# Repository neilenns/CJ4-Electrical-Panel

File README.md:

# CJ4 electrical panel for use with MobiFlight

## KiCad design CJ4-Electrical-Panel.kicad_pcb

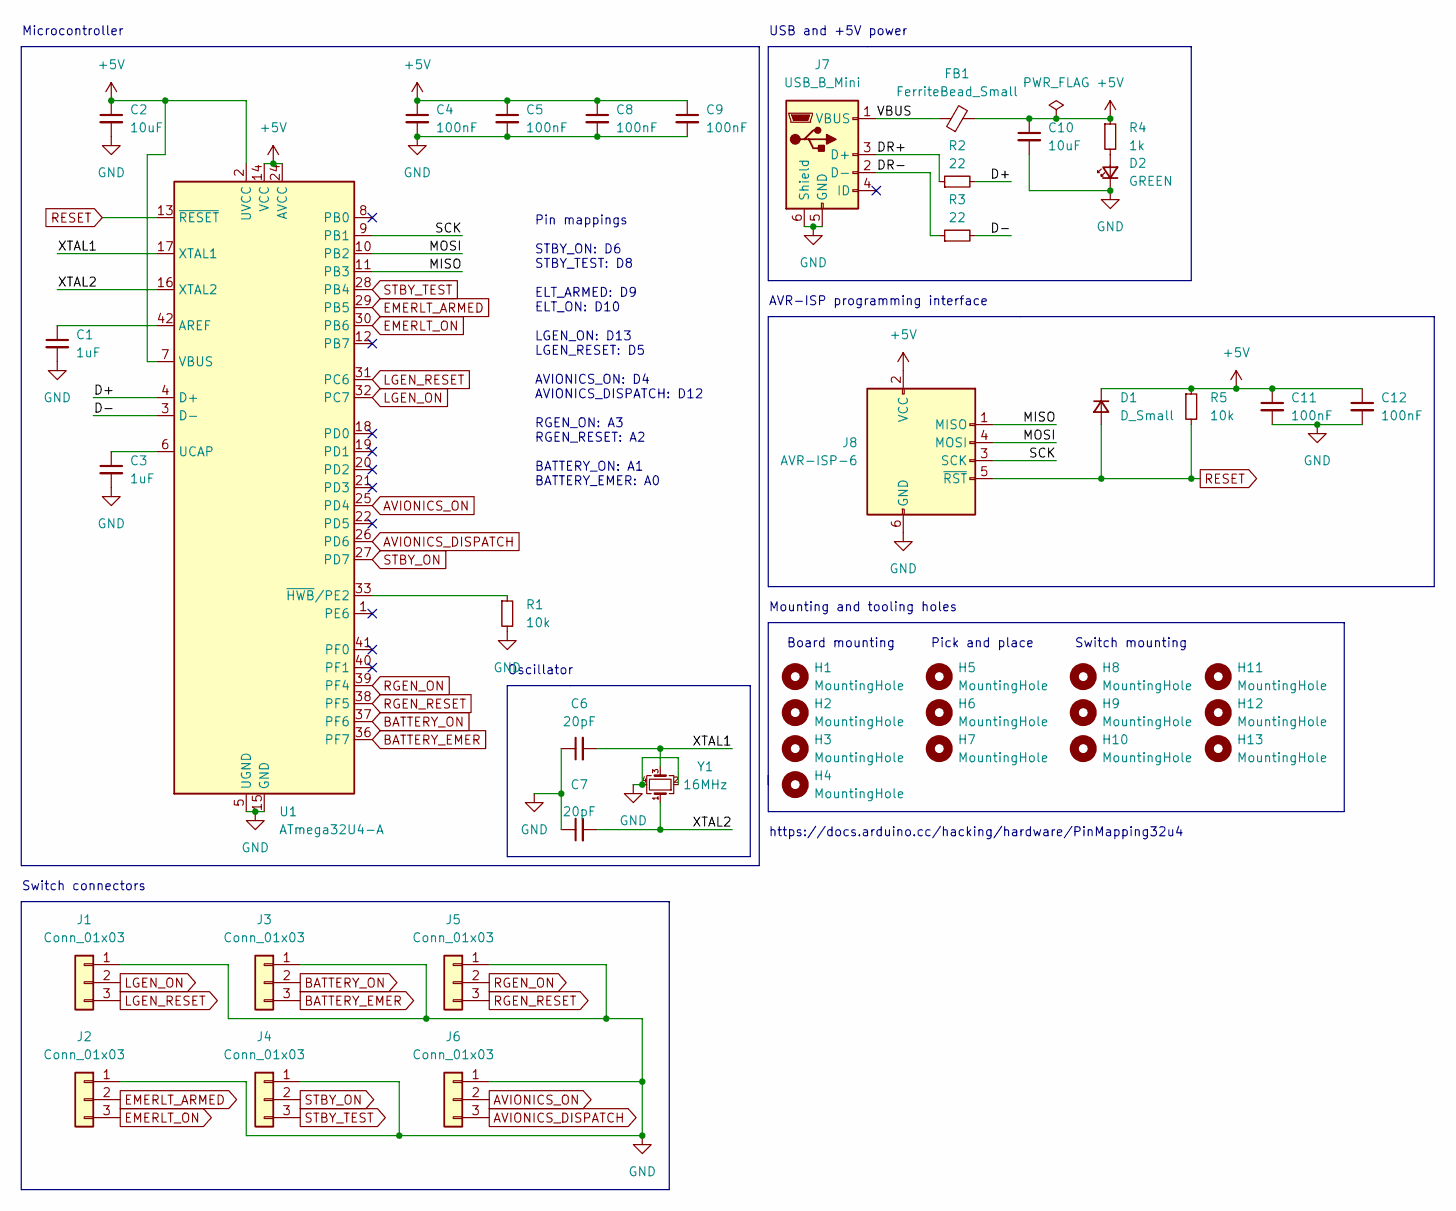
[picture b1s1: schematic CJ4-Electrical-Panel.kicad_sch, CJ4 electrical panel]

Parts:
C1, C3: 1uF; Perfect_0402; JLC 0402
C2, C10: 10uF; Perfect_0402; JLC 0402
C4, C5, C8, C9, C11, C12: 100nF; Perfect_0402; JLC 0402
C6, C7: 20pF; Perfect_0402; JLC 0402
D1: D_Small; D_SOD-323F; JLC SOD-323F
D2: GREEN; LED_0805_2012Metric_Pad1.15x1.40mm_HandSolder; JLC DNP
FB1: FerriteBead_Small; C_0805_2012Metric; JLC 0805
H1, H2, H3, H4: MountingHole; MountingHole_3.2mm_M3; JLC DNP
H5, H6, H7: MountingHole; JLCPCB_Tooling_Hole; JLC DNP
H8, H9, H10, H11, H12, H13: MountingHole; MiniToggleSPDT_screw_mount; JLC DNP
J1, J2, J3, J4, J5, J6: Conn_01x03; JST_XH_B3B-XH-A_1x03_P2.50mm_Vertical; JLC DNP
J7: USB_B_Mini; USB_B_Mini_Amphenol_UE25BE5510H
J8: AVR-ISP-6; Tag-Connect_TC2030-IDC-NL_2x03_P1.27mm_Vertical; JLC DNP
R1, R5: 10k; Perfect_0402; JLC 0402
R2, R3: 22; Perfect_0402; JLC 0402
R4: 1k; Perfect_0402; JLC 0402
U1: ATmega32U4-A; TQFP-44_10x10mm_P0.8mm; JLC DNP
Y1: 16MHz; Crystal_SMD_3225-4Pin_3.2x2.5mm; JLC SMD-CRY-3225_4P

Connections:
+5V: C2.1, C4.1, C5.1, C8.1, C9.1, C10.1, C11.1, C12.1, D1.1 (K), FB1.2, J8.2 (VCC), R4.1, R5.1, U1.2 (UVCC), U1.7 (VBUS), U1.14 (VCC), U1.24 (AVCC), U1.34 (VCC), U1.44 (AVCC)
/D+: R2.2, U1.4 (D+)
/D-: R3.2, U1.3 (D-)
/DR+: J7.3 (D+), R2.1
/DR-: J7.2 (D-), R3.1
/MISO: J8.1 (MISO), U1.11 (PB3)
/MOSI: J8.4 (MOSI), U1.10 (PB2)
/SCK: J8.3 (SCK), U1.9 (PB1)
/VBUS: FB1.1, J7.1 (VBUS)
/XTAL1: C6.2, U1.17 (XTAL1), Y1.3
/XTAL2: C7.2, U1.16 (XTAL2), Y1.1
AVIONICS_DISPATCH: J6.3, U1.26 (PD6)
AVIONICS_ON: J6.2, U1.25 (PD4)
BATTERY_EMER: J3.3, U1.36 (PF7)
BATTERY_ON: J3.2, U1.37 (PF6)
EMERLT_ARMED: J2.2, U1.29 (PB5)
EMERLT_ON: J2.3, U1.30 (PB6)
GND: C1.2, C2.2, C3.2, C4.2, C5.2, C6.1, C7.1, C8.2, C9.2, C10.2, C11.2, C12.2, D2.1 (K), J1.1, J2.1, J3.1, J4.1, J5.1, J6.1, J7.5 (GND), J7.6 (Shield), J8.6 (GND), R1.2, U1.5 (UGND), U1.15 (GND), U1.23 (GND), U1.35 (GND), U1.43 (GND), Y1.2, Y1.4
LGEN_ON: J1.2, U1.32 (PC7)
LGEN_RESET: J1.3, U1.31 (PC6)
unnamed: C1.1, U1.42 (AREF)
unnamed: C3.1, U1.6 (UCAP)
unnamed: D2.2 (A), R4.2
unnamed: R1.1, U1.33 (~HWB/PE2)
RESET: D1.2 (A), J8.5 (~RST), R5.2, U1.13 (~RESET)
RGEN_ON: J5.2, U1.39 (PF4)
RGEN_RESET: J5.3, U1.38 (PF5)
STBY_ON: J4.2, U1.27 (PD7)
STBY_TEST: J4.3, U1.28 (PB4)

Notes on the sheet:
Pick and place
Pin mappings STBY_ON: D6 STBY_TEST: D8 ELT_ARMED: D9 ELT_ON: D10 LGEN_ON: D13 LGEN_RESET: D5 AVIONICS_ON: D4 AVIONICS_DISPATCH: D12 RGEN_ON: A3 RGEN_RESET: A2 BATTERY_ON: A1 BATTERY_EMER: A0
AVR-ISP programming interface
Switch mounting
Board mounting
Microcontroller
Oscillator
Switch connectors
https://docs.arduino.cc/hacking/hardware/PinMapping32u4
Mounting and tooling holes
USB and +5V power

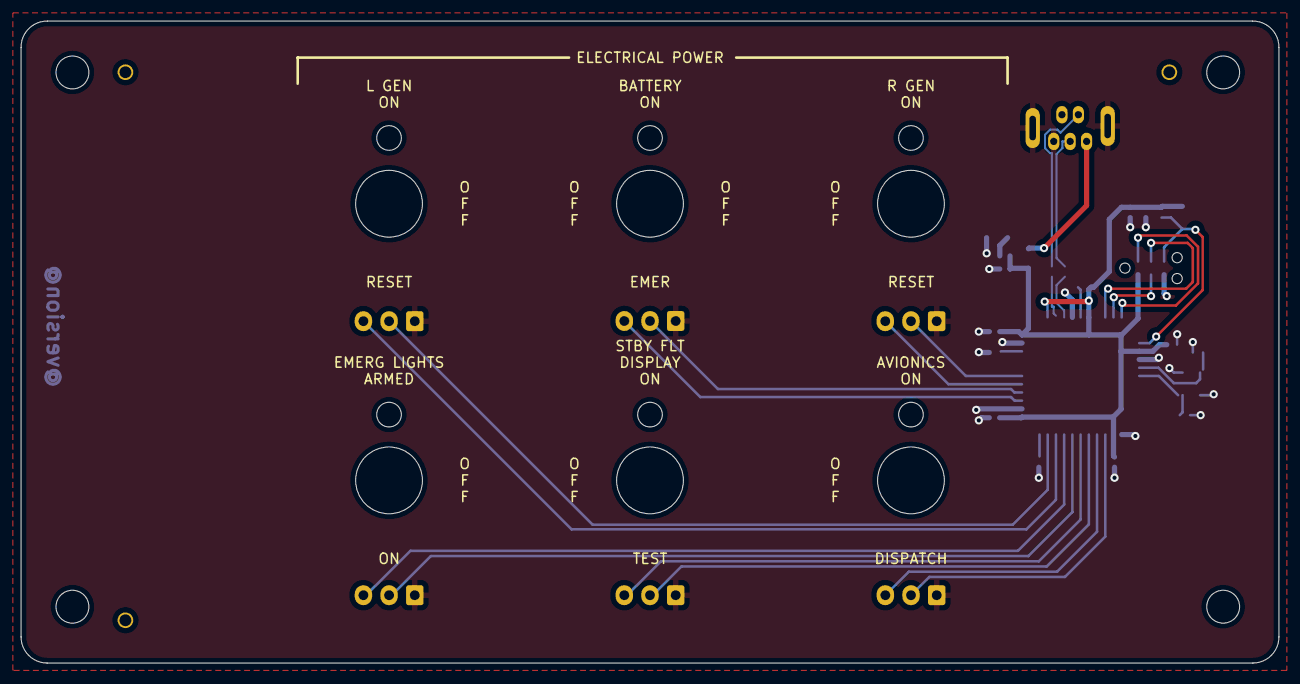
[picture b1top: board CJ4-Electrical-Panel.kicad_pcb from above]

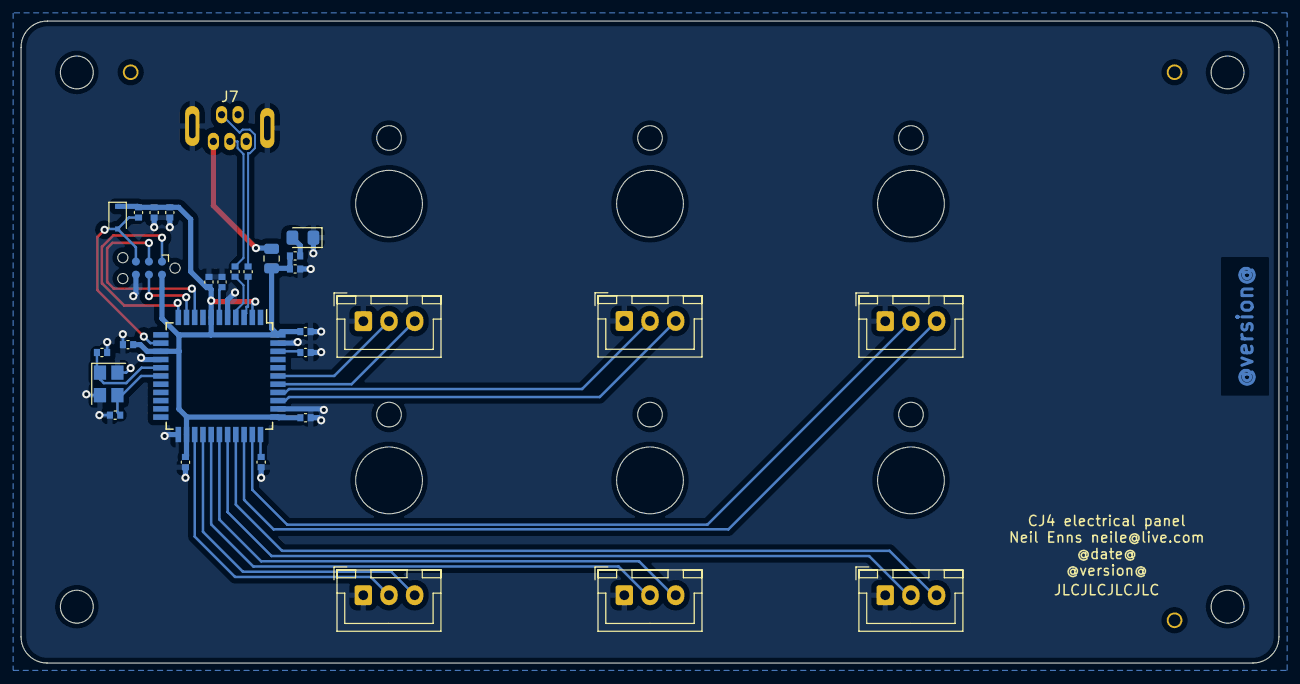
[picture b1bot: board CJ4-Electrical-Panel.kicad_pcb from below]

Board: 2 copper layers, 122.4 x 62.5 mm, 43 parts (30 on the bottom side), 29 nets.

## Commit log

2022-02-06 Initial work
2022-02-06 Finish routing, add JLCPCB part numbers
2022-02-06 Update to KiCad v6 automation
2022-02-06 Add date and version placeholders
2022-02-06 Add missing starting date
2022-02-07 All routed and ready for fab
2022-02-07 Correct footprint error, add USB render
2022-02-18 Change USB connector, add missing labels
2022-07-01 Fixes Make switch holes bigger #2
2022-07-01 Replace USB connector Fixes #1
2022-07-12 Move USB footprint to back of board
2022-07-12 Update to newer kibot image Fixes #7
2022-07-12 Update kibot docker image Fixes #9
2022-07-24 Add MobiFlight module config
2022-10-09 Fix 3D models for Fusion 360
2025-02-25 Add renovate.json
